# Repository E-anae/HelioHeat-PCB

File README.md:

# Projet ELEC - PCB

## Architecture

Cette section présente l'architecture d'un thermomètre autonome fonctionnant à
l'aide d'un panneau solaire. L'objectif est de mesurer la température d'un lieu
et d'afficher sur des afficheurs 7 segments tout en assurant une alimentation
énergétique durable à l'aide d'une batterie rechargeable.

### Composants principaux

Les composants que nous utiliserons sont les suivants :

| Référence | Composant | Quantité | Remarques |
| --------- | -------------- | -------------- | ---- |
| ATTINY85 | Microcontrôleur | 1 | Gestion des capteurs et de l'affichage |
| MCP9700AT-E/LT | Capteur de température | 1 | Mesure de la température |
| 157119S12801 | Afficheur 7 segments | 3 | Affiche numérique de la température |
| PET Solar panel | Mini panneau solaire | 1 | Recharge la batterie |
| CD4511 | Décodeur BCD vers 7 segments | 3 | Simplifie le pilottage de l'afficheur |
| | Batterie rechargeable | 1 | Alimentation autonome |
| 74HC595 | Registre à décalage | 2 | Sérialisation des données |

### Schéma fonctionnel

1. Le panneau solaire charge la batterie via un circuit de gestion de charge.
2. La batterie alimente le microcontrôleur et les afficheurs 7 segments.
3. Le microcontrôleur lit la température via le capteur et affiche les valeurs
sur les afficheurs 7 segments.

Le schéma fonctionnel est présent dans le document `documents/schema.pdf`.

Ce projet permettra de développer une solution autonome et durable pour la
mesure de la température. La conception d'une carte PCB optimisera l'intégration
des composants et la gestion énergétique.

## Fonction de transfert du capteur de température

La fonction de transfert du capteur de température est explicitée dans la partie
4 (*Applications information*) de la fiche de donnée du capteur de température
(`documents/thermal_sensor_datasheet.pdf`).

Cette dernière nous informe que

$$
V_{OUT} = T_C \times T_A + V_{0°C}
$$

avec $V_{OUT}$ la tension de sortie du capteur, $T_C$ le coefficient de
température, $T_A$ la température ambiante et $V_{0°C}$ la tension de sortie du
capteur à 0°C.

On a alors,

$$
\begin{align*}
    V_{OUT} &= T_C \times T_A + V_{0°C} \\
    V_{OUT} - V_{0°C} &= T_C \times T_A \\
    T_A &= \frac{V_{OUT} - V_{0°C}}{T_C}
\end{align*}
$$

avec $V_{0°C} = 500 V$ et $T_C = 10.0 V$.

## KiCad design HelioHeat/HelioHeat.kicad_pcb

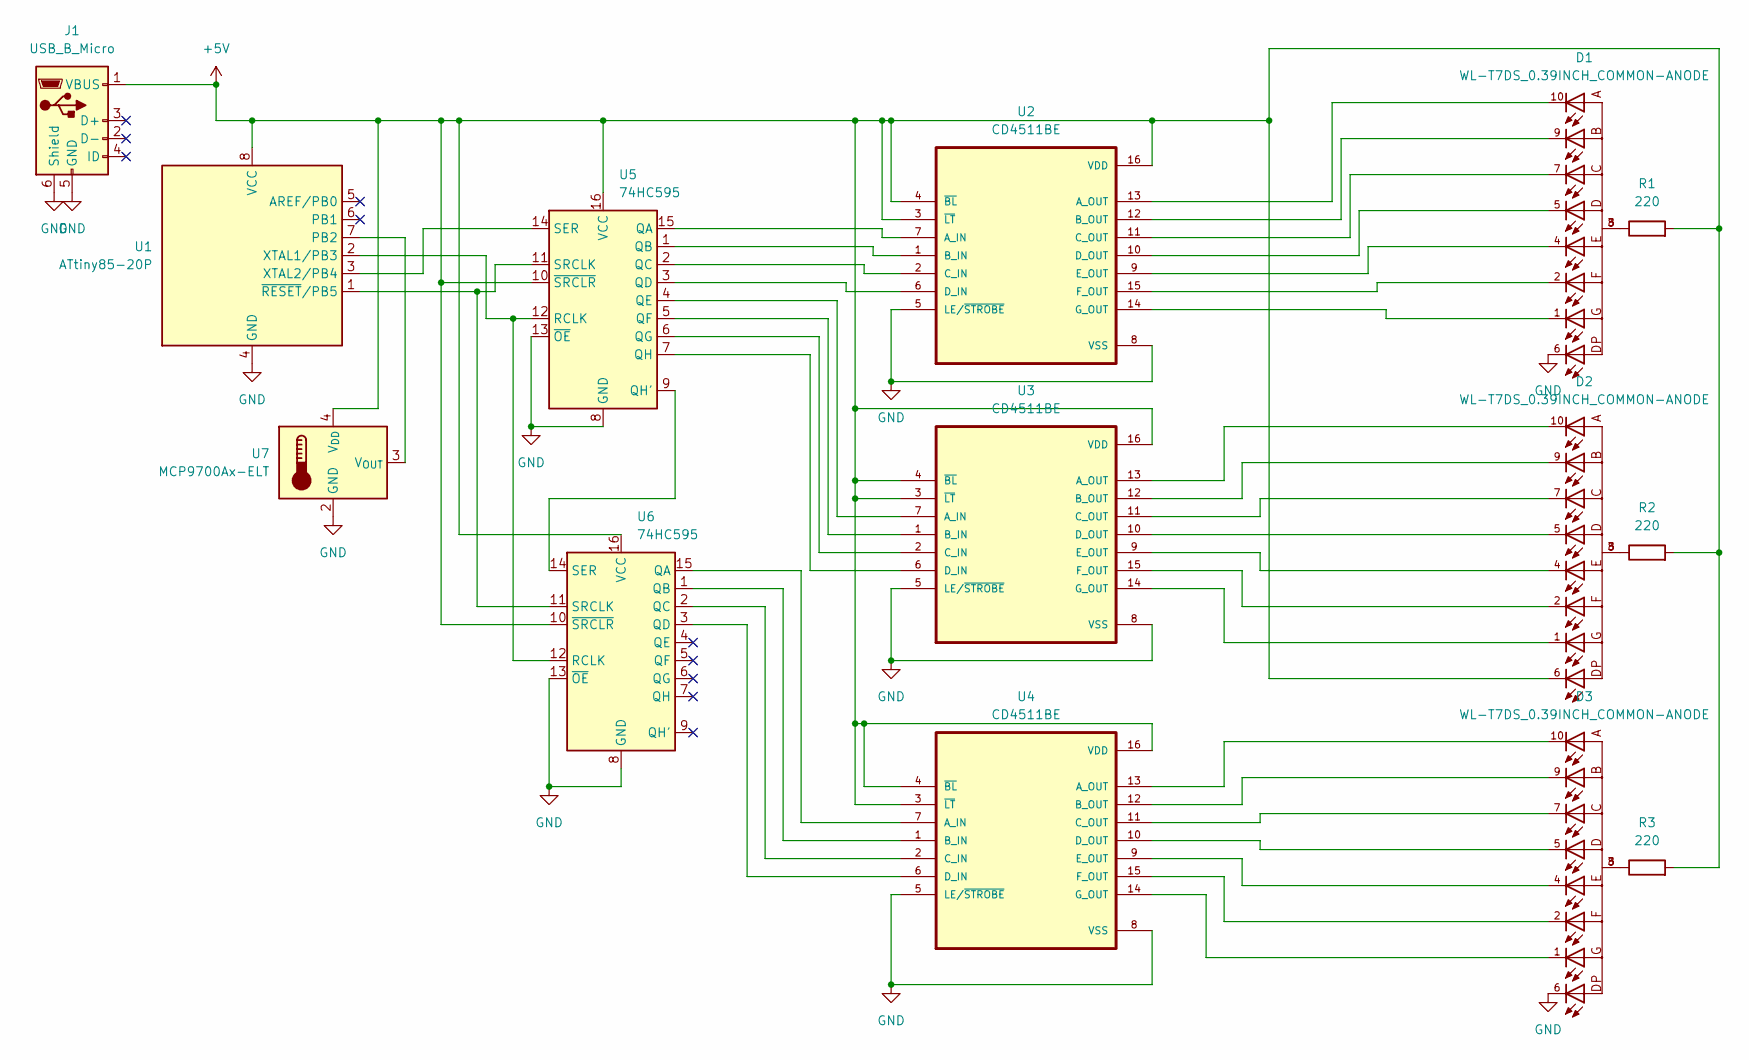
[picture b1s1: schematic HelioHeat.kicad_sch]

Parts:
D1, D2, D3: WL-T7DS_0.39INCH_COMMON-ANODE; WL-T7DS_0.39INCH
J1: USB_B_Micro; USB_Micro-B_Amphenol_10103594-0001LF_Horizontal
R1, R2, R3: 220; R_0201_0603Metric
U1: ATtiny85-20P; DIP-8_W7.62mm
U2, U3, U4: CD4511BE; DIP794W45P254L1969H508Q16
U5, U6: 74HC595; SO16
U7: MCP9700Ax-ELT; SOT-353_SC-70-5

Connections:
+5V: D2.6, J1.1 (VBUS), R1.2, R2.2, R3.2, U1.8 (VCC), U2.3 (~LT), U2.4 (~BL), U2.16 (VDD), U3.3 (~LT), U3.4 (~BL), U3.16 (VDD), U4.3 (~LT), U4.4 (~BL), U4.16 (VDD), U5.10 (~SRCLR), U5.16 (VCC), U6.10 (~SRCLR), U6.16 (VCC), U7.4 (V_{DD})
GND: D1.6, D3.6, J1.5 (GND), J1.6 (Shield), U1.4 (GND), U2.5 (LE/~STROBE), U2.8 (VSS), U3.5 (LE/~STROBE), U3.8 (VSS), U4.5 (LE/~STROBE), U4.8 (VSS), U5.8 (GND), U5.13 (~OE), U6.8 (GND), U6.13 (~OE), U7.2 (GND)
unnamed: D1.3, D1.8, R1.1
unnamed: D2.3, D2.8, R2.1
unnamed: D3.3, D3.8, R3.1
unnamed: U1.7 (PB2), U7.3 (V_{OUT})
unnamed: U1.2 (XTAL1/PB3), U5.12 (RCLK), U6.12 (RCLK)
unnamed: U1.3 (XTAL2/PB4), U5.14 (SER)
unnamed: U1.1 (~RESET/PB5), U5.11 (SRCLK), U6.11 (SRCLK)
unnamed: U2.7 (A_IN), U5.15 (QA)
unnamed: D1.10, U2.13 (A_OUT)
unnamed: U2.1 (B_IN), U5.1 (QB)
unnamed: D1.9, U2.12 (B_OUT)
unnamed: U2.2 (C_IN), U5.2 (QC)
unnamed: D1.7, U2.11 (C_OUT)
unnamed: U2.6 (D_IN), U5.3 (QD)
unnamed: D1.5, U2.10 (D_OUT)
unnamed: D1.4, U2.9 (E_OUT)
unnamed: D1.2, U2.15 (F_OUT)
unnamed: D1.1, U2.14 (G_OUT)
unnamed: U3.7 (A_IN), U5.4 (QE)
unnamed: D2.10, U3.13 (A_OUT)
unnamed: U3.1 (B_IN), U5.5 (QF)
unnamed: D2.9, U3.12 (B_OUT)
unnamed: U3.2 (C_IN), U5.6 (QG)
unnamed: D2.7, U3.11 (C_OUT)
unnamed: U3.6 (D_IN), U5.7 (QH)
unnamed: D2.5, U3.10 (D_OUT)
unnamed: D2.4, U3.9 (E_OUT)
unnamed: D2.2, U3.15 (F_OUT)
unnamed: D2.1, U3.14 (G_OUT)
unnamed: U4.7 (A_IN), U6.15 (QA)
unnamed: D3.10, U4.13 (A_OUT)
unnamed: U4.1 (B_IN), U6.1 (QB)
unnamed: D3.9, U4.12 (B_OUT)
unnamed: U4.2 (C_IN), U6.2 (QC)
unnamed: D3.7, U4.11 (C_OUT)
unnamed: U4.6 (D_IN), U6.3 (QD)
unnamed: D3.5, U4.10 (D_OUT)
unnamed: D3.4, U4.9 (E_OUT)
unnamed: D3.2, U4.15 (F_OUT)
unnamed: D3.1, U4.14 (G_OUT)
unnamed: U5.9 (QH'), U6.14 (SER)

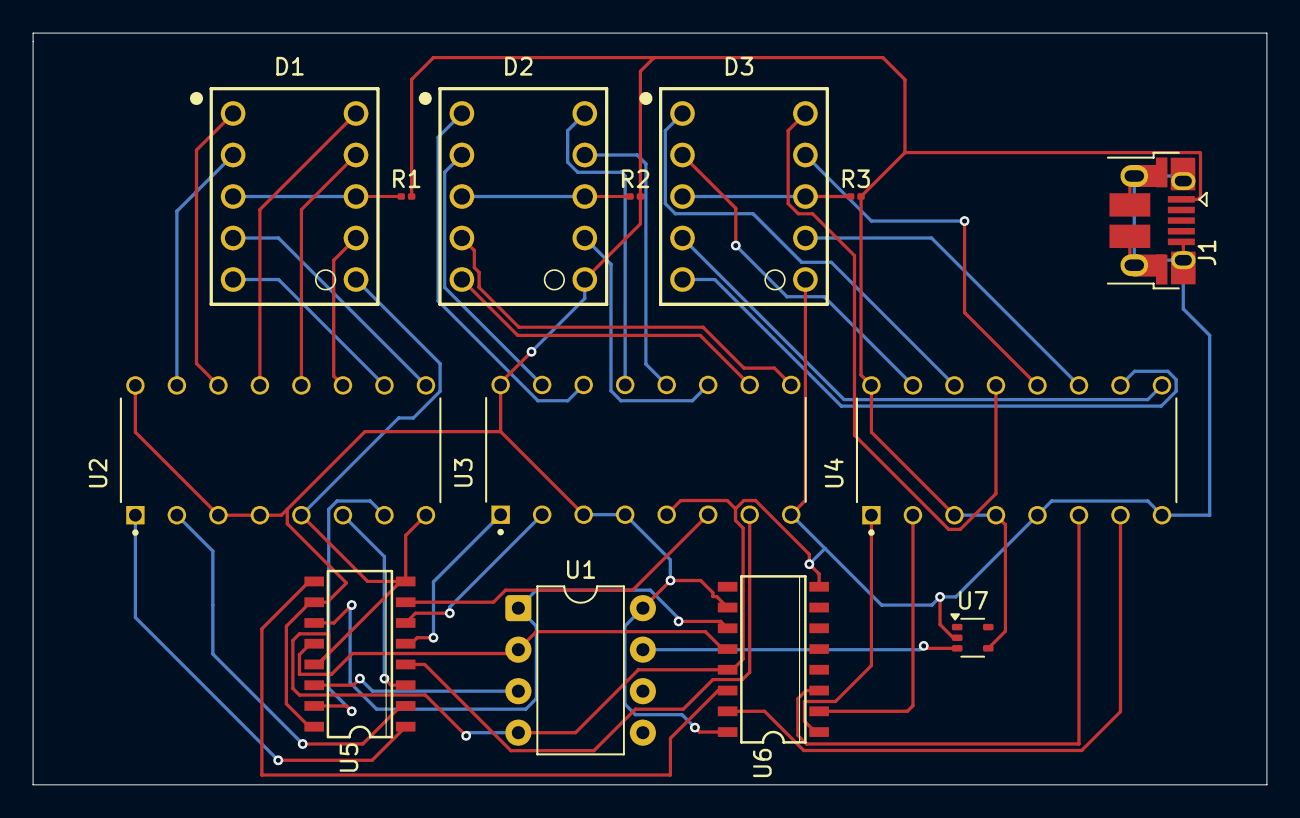
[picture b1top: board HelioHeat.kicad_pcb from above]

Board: 2 copper layers, 75.5 x 46.0 mm, 14 parts (0 on the bottom side), 43 nets.

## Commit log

2025-04-16 datasheet
2025-04-16 feat(documentation): add architecture
2025-04-16 feat(documentation): add equation to find temperature
2025-04-16 fix(documentation): latex typo
2025-04-24 feat: add missing pieces
2025-05-06 cables
2025-05-06 quick adjusment
2025-05-06 fixes
2025-05-07 i am a routeur
2025-05-07 fix(documentation): typo latex
2025-05-07 feat: add output files
2025-06-27 feat: add plan test
